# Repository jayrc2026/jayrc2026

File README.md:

- 👋 Hi, I’m @Jay_R_Chotaliya
- 👀 I’m interested in Linuz_Embedded_Systems_C
- 🌱 I’m currently learning Linux_C
- 💞️ I’m looking to collaborate on Hardware designs
- 📫 How to reach me jaychotaliya2468@gmail.com

<!---
jayrc2026/jayrc2026 is a ✨ special ✨ repository because its `README.md` (this file) appears on your GitHub profile.
You can click the Preview link to take a look at your changes.
--->

<picture>
  <source media="(prefers-color-scheme: dark)" srcset="https://raw.githubusercontent.com/jayrc2026/jayrc2026/output/github-snake-dark.svg" />
  <source media="(prefers-color-scheme: light)" srcset="https://raw.githubusercontent.com/jayrc2026/jayrc2026/output/github-snake.svg" />
  
</picture>

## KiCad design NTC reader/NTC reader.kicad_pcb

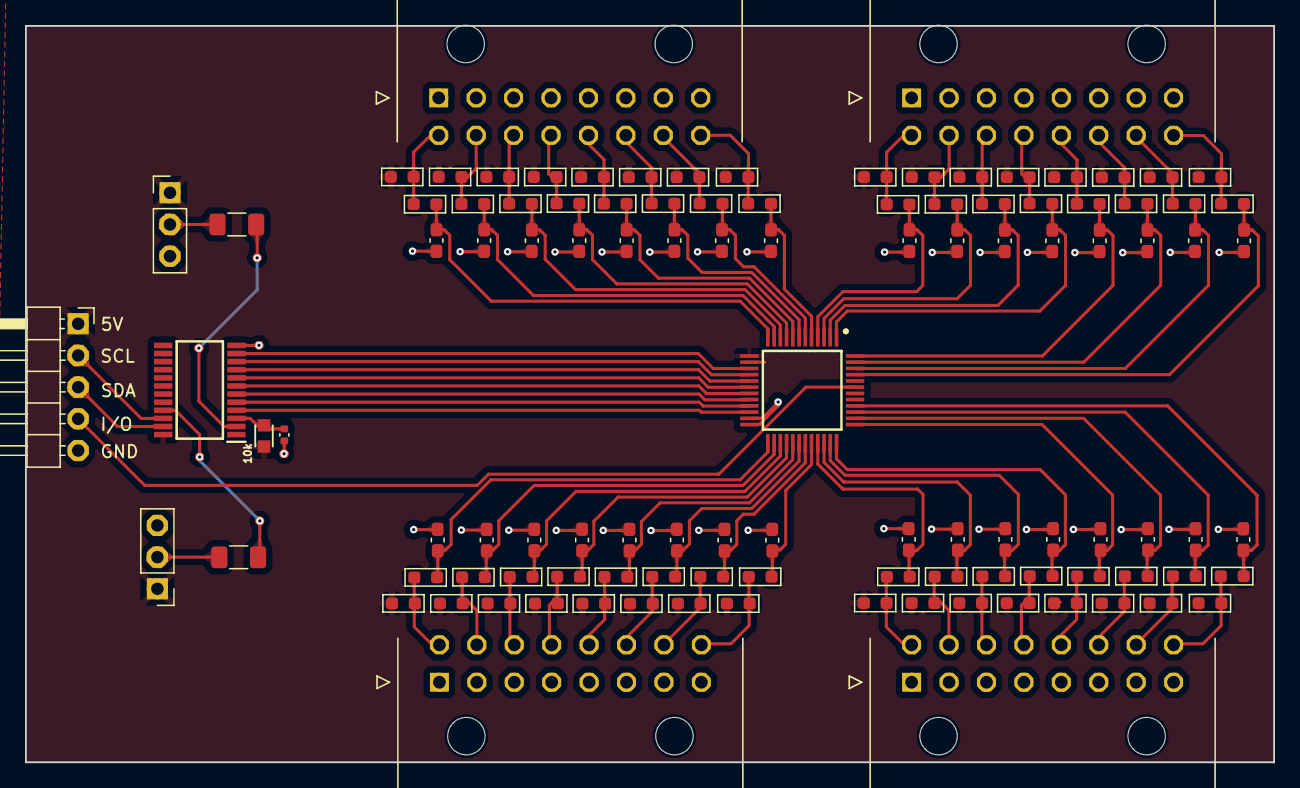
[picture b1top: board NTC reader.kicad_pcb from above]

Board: 2 copper layers, 100.1 x 59.0 mm, 109 parts (0 on the bottom side), 82 nets.

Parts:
C1: 0.1uF; C_0402_1005Metric
C2, C3, C4, C5, C6, C7, C8, C9, C10, C11, C12, C13, C14, C15, C16, C17, C18, C19, C20, C21, C22, C23, C24, C25, C26, C27, C28, C29, C30, C31, C32, C33: 10uF; C_0603_1608Metric_Pad1.08x0.95mm_HandSolder
IC1: ADG732BSUZ-REEL; QFP50P900X900X120-48N
IC2: PCA9539RPW_118; SOP65P640X110-24N
J1, J2, J6, J7: 43045-1602; 43045-16_00,01,02,10_
J3: Conn_01x05_Pin; PinHeader_1x05_P2.54mm_Horizontal
J4, J5: Conn_01x03_Pin; PinHeader_1x03_P2.54mm_Vertical
R1: 10k; R_0603
R2, R3: 22; R_1206_3216Metric_Pad1.30x1.75mm_HandSolder
R4, R5, R6, R7, R8, R9, R10, R11, R20, R21, R22, R23, R24, R25, R26, R27, R36, R37, R38, R39, R40, R41, R42, R43, R52, R53, R54, R55, R56, R57, R58, R59: 10k; R_0603_1608Metric_Pad0.98x0.95mm_HandSolder
R12, R13, R14, R15, R16, R17, R18, R19, R28, R29, R30, R31, R32, R33, R34, R35, R44, R45, R46, R47, R48, R49, R50, R51, R60, R61, R62, R63, R64, R65, R66, R67: 100R; R_0603_1608Metric_Pad0.98x0.95mm_HandSolder

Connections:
+5V: IC1.13 (VDD_1), IC1.14 (VDD_2), IC2.24 (VDD), J3.1, J4.1, J5.1, R1.1, R4.1, R5.1, R6.1, R7.1, R8.1, R9.1, R10.1, R11.1, R20.1, R21.1, R22.1, R23.1, R24.1, R25.1, R26.1, R27.1, R36.1, R37.1, R38.1, R39.1, R40.1, R41.1, R42.1, R43.1, R52.1, R53.1, R54.1, R55.1, R56.1, R57.1, R58.1, R59.1
/ADG_TEMP_Sense/A0: IC1.15 (A0), IC2.11 (IO0_7)
/ADG_TEMP_Sense/A1: IC1.16 (A1), IC2.10 (IO0_6)
/ADG_TEMP_Sense/A2: IC1.17 (A2), IC2.9 (IO0_5)
/ADG_TEMP_Sense/A3: IC1.18 (A3), IC2.8 (IO0_4)
/ADG_TEMP_Sense/A4: IC1.19 (A4), IC2.7 (IO0_3)
/ADG_TEMP_Sense/CS: IC1.20 (~CS), IC2.6 (IO0_2)
/ADG_TEMP_Sense/EN: IC1.22 (~EN), IC2.4 (IO0_0)
/ADG_TEMP_Sense/F_Temp_1: C2.1, IC1.12 (S1), R12.2
/ADG_TEMP_Sense/F_Temp_2: C10.1, IC1.11 (S2), R28.2
/ADG_TEMP_Sense/F_Temp_3: C18.1, IC1.10 (S3), R44.2
/ADG_TEMP_Sense/F_Temp_4: C26.1, IC1.9 (S4), R60.2
/ADG_TEMP_Sense/F_Temp_5: C3.1, IC1.8 (S5), R13.2
/ADG_TEMP_Sense/F_Temp_6: C11.1, IC1.7 (S6), R29.2
/ADG_TEMP_Sense/F_Temp_7: C19.1, IC1.6 (S7), R45.2
/ADG_TEMP_Sense/F_Temp_8: C27.1, IC1.5 (S8), R61.2
/ADG_TEMP_Sense/F_Temp_9: C4.1, IC1.4 (S9), R14.2
/ADG_TEMP_Sense/F_Temp_10: C12.1, IC1.3 (S10), R30.2
/ADG_TEMP_Sense/F_Temp_11: C20.1, IC1.2 (S11), R46.2
/ADG_TEMP_Sense/F_Temp_12: C28.1, IC1.1 (S12), R62.2
/ADG_TEMP_Sense/F_Temp_13: C5.1, IC1.48 (S13), R15.2
/ADG_TEMP_Sense/F_Temp_14: C13.1, IC1.47 (S14), R31.2
/ADG_TEMP_Sense/F_Temp_15: C21.1, IC1.46 (S15), R47.2
/ADG_TEMP_Sense/F_Temp_16: C29.1, IC1.45 (S16), R63.2
/ADG_TEMP_Sense/F_Temp_17: C6.1, IC1.25 (S17), R16.2
/ADG_TEMP_Sense/F_Temp_18: C14.1, IC1.26 (S18), R32.2
/ADG_TEMP_Sense/F_Temp_19: C22.1, IC1.27 (S19), R48.2
/ADG_TEMP_Sense/F_Temp_20: C30.1, IC1.28 (S20), R64.2
/ADG_TEMP_Sense/F_Temp_21: C7.1, IC1.29 (S21), R17.2
/ADG_TEMP_Sense/F_Temp_22: C15.1, IC1.30 (S22), R33.2
/ADG_TEMP_Sense/F_Temp_23: C23.1, IC1.31 (S23), R49.2
/ADG_TEMP_Sense/F_Temp_24: C31.1, IC1.32 (S24), R65.2
/ADG_TEMP_Sense/F_Temp_25: C8.1, IC1.33 (S25), R18.2
/ADG_TEMP_Sense/F_Temp_26: C16.1, IC1.34 (S26), R34.2
/ADG_TEMP_Sense/F_Temp_27: C24.1, IC1.35 (S27), R50.2
/ADG_TEMP_Sense/F_Temp_28: C32.1, IC1.36 (S28), R66.2
/ADG_TEMP_Sense/F_Temp_29: C9.1, IC1.37 (S29), R19.2
/ADG_TEMP_Sense/F_Temp_30: C17.1, IC1.38 (S30), R35.2
/ADG_TEMP_Sense/F_Temp_31: C25.1, IC1.39 (S31), R51.2
/ADG_TEMP_Sense/F_Temp_32: C33.1, IC1.40 (S32), R67.2
/ADG_TEMP_Sense/WR: IC1.21 (~WR), IC2.5 (IO0_1)
/I_O_Expander/I2C_A0: IC2.21 (A0), R3.2
/I_O_Expander/I2C_A1: IC2.2 (A1), R2.2
/I_O_Expander/RESET: C1.1, IC2.3 (~RESET), R1.2
/I_O_Expander/SCL: IC2.22 (SCL), J3.2
/I_O_Expander/SDA: IC2.23 (SDA), J3.3
/I/O: IC1.43 (D), J3.4
/Temp_1: J2.9, R4.2, R12.1
/Temp_2: J2.10, R20.2, R28.1
/Temp_3: J2.11, R36.2, R44.1
/Temp_4: J2.12, R52.2, R60.1
/Temp_5: J2.13, R5.2, R13.1
/Temp_6: J2.14, R21.2, R29.1
/Temp_7: J2.15, R37.2, R45.1
/Temp_8: J2.16, R53.2, R61.1
/Temp_9: J1.9, R6.2, R14.1
/Temp_10: J1.10, R22.2, R30.1
/Temp_11: J1.11, R38.2, R46.1
/Temp_12: J1.12, R54.2, R62.1
/Temp_13: J1.13, R7.2, R15.1
/Temp_14: J1.14, R23.2, R31.1
/Temp_15: J1.15, R39.2, R47.1
/Temp_16: J1.16, R55.2, R63.1
/Temp_17: J6.9, R8.2, R16.1
/Temp_18: J6.10, R24.2, R32.1
/Temp_19: J6.11, R40.2, R48.1
/Temp_20: J6.12, R56.2, R64.1
/Temp_21: J6.13, R9.2, R17.1
/Temp_22: J6.14, R25.2, R33.1
/Temp_23: J6.15, R41.2, R49.1
/Temp_24: J6.16, R57.2, R65.1
/Temp_25: J7.9, R10.2, R18.1
/Temp_26: J7.10, R26.2, R34.1
/Temp_27: J7.11, R42.2, R50.1
/Temp_28: J7.12, R58.2, R66.1
/Temp_29: J7.13, R11.2, R19.1
/Temp_30: J7.14, R27.2, R35.1
/Temp_31: J7.15, R43.2, R51.1
/Temp_32: J7.16, R59.2, R67.1
GND: C1.2, C2.2, C3.2, C4.2, C5.2, C6.2, C7.2, C8.2, C9.2, C10.2, C11.2, C12.2, C13.2, C14.2, C15.2, C16.2, C17.2, C18.2, C19.2, C20.2, C21.2, C22.2, C23.2, C24.2, C25.2, C26.2, C27.2, C28.2, C29.2, C30.2, C31.2, C32.2, C33.2, IC1.23 (GND), IC1.24 (VSS), IC2.12 (VSS), J1.1, J1.2, J1.3, J1.4, J1.5, J1.6, J1.7, J1.8, J2.1, J2.2, J2.3, J2.4, J2.5, J2.6, J2.7, J2.8, J3.5, J4.3, J5.3, J6.1, J6.2, J6.3, J6.4, J6.5, J6.6, J6.7, J6.8, J7.1, J7.2, J7.3, J7.4, J7.5, J7.6, J7.7, J7.8
unnamed: J4.2, R2.1
unnamed: J5.2, R3.1

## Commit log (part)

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2025-10-11 Update snake animation [skip ci] b9cc06b2751cd8ac86bb95bf8ec38bb41124148d
